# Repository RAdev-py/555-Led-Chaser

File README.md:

# 555 LED Chaser PCB

---

## What is this?

This is a **555 LED Chaser** — a PCB that blinks 10 LEDs in a looping pattern.

I made this project to learn the basics of PCB design and by following the guided tutorial on the BluePrint website. I still have a lot to learn but this was a good start to learning how to use some of the tools.

---
## PCB

The board was designed in **KiCad**. It is a 2-layer PCB kept under 100×100mm. The outline is in the shape of Appa from Avatar the Last Airbender, a show that I love with all my heart.

---

## Schematic / Wiring Diagram

## Bill of Materials (BOM)

| # | Component | Value / Part | Qty | Link |
|---|-----------|-------------|-----|------|
| 1 | 555 Timer IC | [NE555P](https://www.digikey.com/en/products/detail/texas-instruments/NE555P/277735) | 1 | [DigiKey](https://www.digikey.com/en/products/detail/texas-instruments/NE555P/277735) |
| 2 | Decade Counter IC | [CD4017BE](https://www.digikey.com/en/products/detail/texas-instruments/CD4017BE/67073) | 1 | [DigiKey](https://www.digikey.com/en/products/detail/texas-instruments/CD4017BE/67073) |
| 3 | Resistor | 1kΩ | 2 | [DigiKey](https://www.digikey.com/en/products/detail/yageo/CFR-25JB-52-1K/338) |
| 4 | Resistor | 470Ω | 1 | [DigiKey](https://www.digikey.com/en/products/detail/yageo/CFR-25JB-52-470R/343) |
| 5 | Potentiometer | 100kΩ | 1 | [DigiKey](https://www.digikey.com/en/products/detail/bourns-inc/3386P-1-104LF/1088979) |
| 6 | Electrolytic Capacitor | 10µF | 1 | [DigiKey](https://www.digikey.com/en/products/detail/panasonic-electronic-components/ECA-1HM100/245067) |
| 7 | Ceramic Capacitor | 0.01µF | 1 | [DigiKey](https://www.digikey.com/en/products/detail/kemet/C320C103K5R5TA/818254) |
| 8 | LEDs (assorted colors) | 5mm through-hole | 10 | [DigiKey](https://www.digikey.com/en/products/detail/kingbright/WP7113ID/1747663) |
| 9 | Pin Header (power) | 1×2 | 2 | [DigiKey](https://www.digikey.com/en/products/detail/adam-tech/PH2-02-UA/9830344) |
| 10 | PCB | Custom, 2-layer | 1 | [JLCPCB](https://jlcpcb.com) |

---

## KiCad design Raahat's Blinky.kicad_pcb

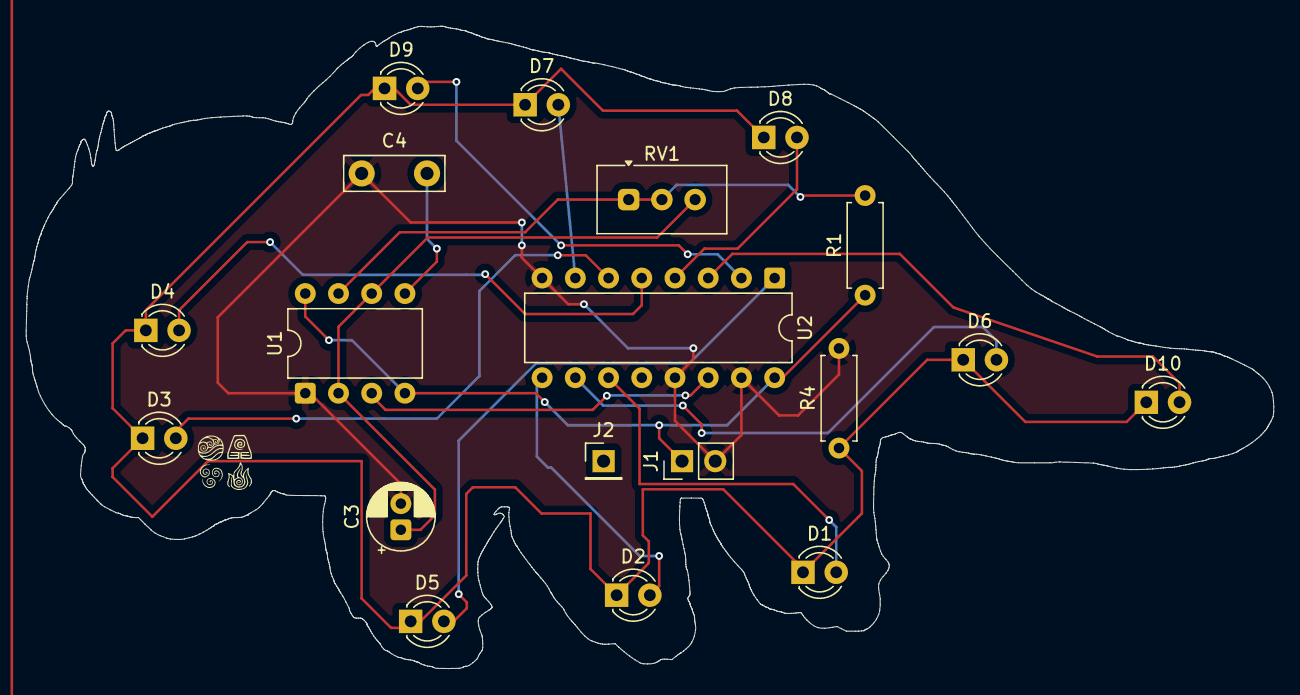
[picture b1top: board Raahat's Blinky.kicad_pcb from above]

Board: 2 copper layers, 95.4 x 49.1 mm, 19 parts (0 on the bottom side), 17 nets.

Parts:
C3: 1 uF; CP_Radial_D5.0mm_P2.00mm
C4: 0.01 uF; C_Disc_D7.5mm_W2.5mm_P5.00mm
D1: D1LED; LED_D3.0mm
D2: D2LED; LED_D3.0mm
D3: D3LED; LED_D3.0mm
D4: D4LED; LED_D3.0mm
D5: D5LED; LED_D3.0mm
D6: D6LED; LED_D3.0mm
D7: D7LED; LED_D3.0mm
D8: D8LED; LED_D3.0mm
D9: D9LED; LED_D3.0mm
D10: D10LED; LED_D3.0mm
J1: Conn_01x02_Socket; PinHeader_1x02_P2.54mm_Vertical
J2: Conn_01x01_Socket; PinHeader_1x01_P2.54mm_Vertical
R1: 1k; R_Axial_DIN0207_L6.3mm_D2.5mm_P7.62mm_Horizontal
R4: 470; R_Axial_DIN0207_L6.3mm_D2.5mm_P7.62mm_Horizontal
RV1: 50k; Potentiometer_Vishay_T93YA_Vertical
U1: NE555P; DIP-8_W7.62mm
U2: 4017; DIP-16_W7.62mm

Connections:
+5V: J1.1, R1.1, U1.4 (R), U1.8 (VCC), U2.16 (VDD)
GND: C3.2, C4.1, J1.2, R4.2, U1.1 (GND), U2.8 (VSS), U2.13 (CKEN), U2.15 (Reset)
unnamed: D1.2 (A), U2.11 (Q9)
unnamed: D1.1 (K), D2.1 (K), D3.1 (K), D4.1 (K), D5.1 (K), D6.1 (K), D7.1 (K), D8.1 (K), D9.1 (K), D10.1 (K), R4.1
unnamed: D2.2 (A), U2.9 (Q8)
unnamed: D3.2 (A), U2.6 (Q7)
unnamed: D4.2 (A), U2.5 (Q6)
unnamed: D5.2 (A), U2.1 (Q5)
unnamed: D6.2 (A), U2.10 (Q4)
unnamed: D7.2 (A), U2.7 (Q3)
unnamed: D8.2 (A), U2.4 (Q2)
unnamed: D9.2 (A), U2.2 (Q1)
unnamed: D10.2 (A), U2.3 (Q0)
unnamed: C4.2, U1.5 (CV)
unnamed: R1.2, RV1.1, RV1.2, U1.7 (DIS)
OUT: U1.3 (Q), U2.14 (CLK)
TR: C3.1, RV1.3, U1.2 (TR), U1.6 (THR)

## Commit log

2026-03-07 wroing
2026-03-07 finished
2026-03-07 finalized read me
2026-03-07 Revise README for clarity and detail
    Updated project description and usage instructions in README.md.
2026-03-07 csv added
2026-03-07 rename PCB_Layout to pcb_layout
2026-03-15 added bom
